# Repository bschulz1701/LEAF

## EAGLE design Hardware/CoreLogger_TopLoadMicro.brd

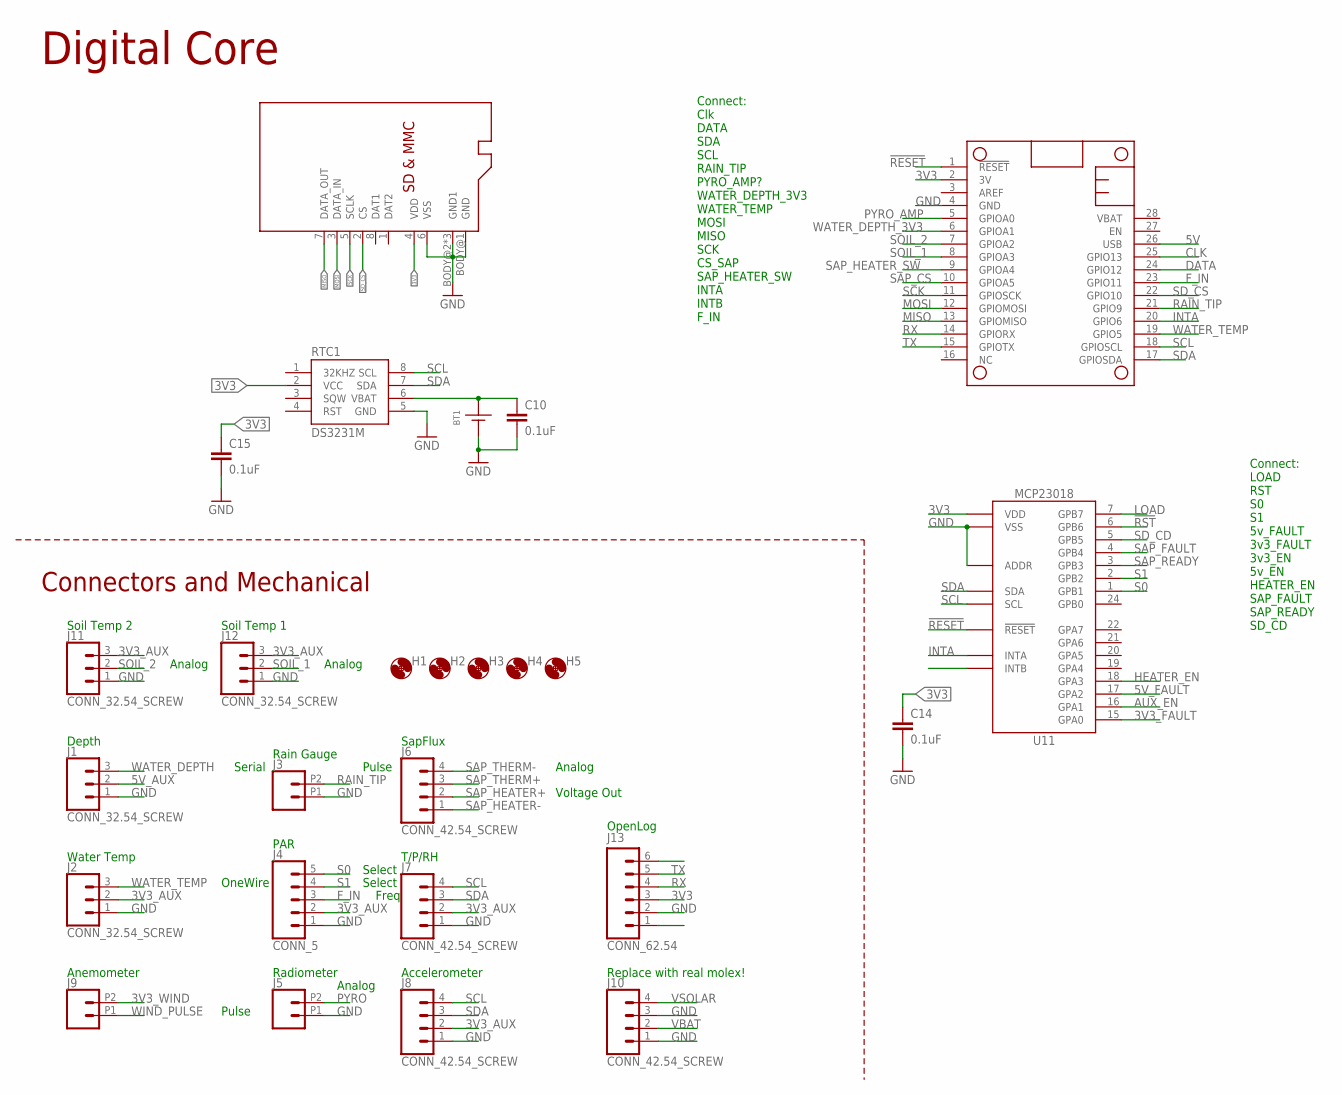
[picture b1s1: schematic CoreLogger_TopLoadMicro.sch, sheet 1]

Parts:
BT1: BATTERY_COIN12MM; LINX_BAT-HLD-012-SMT
C10: 0.1uF; C0603
C14, C15: 0.1uF; C0402
H1, H2, H3, H4, H5: MOUNTING_HOLE4_NP; 4_40
J1, J2, J11, J12: CONN_32.54_SCREW; 1X03_SCREW
J3, J5, J9: CONN_022.54_SCREW; 1X02_2.54_SCREWTERM
J4: CONN_5; 1X05
J6, J7, J8, J10: CONN_42.54_SCREW; 1X04_SCREW
J13: CONN_62.54; 1X06
MS1: FEATHERWING_NODIM; FEATHERWING_DIM
RTC1: DS3231M; SO08
SD1: MICROSD_NOCDHINDGED; USD_MOLEX_HINDGED
U11: MCP23018QFN; QFN24

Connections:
3V3: C14.1, C15.1, J13.3, MS1.2 (3V), RTC1.2 (VCC), SD1.4 (VDD), U11.8 (VDD); also elsewhere on the board
3V3_AUX: J2.2, J4.2, J7.2, J8.2, J11.3, J12.3; also elsewhere on the board
3V3_FAULT: U11.15 (GPA0); also elsewhere on the board
3V3_WIND: J9.P2 (2); also elsewhere on the board
5V: MS1.26 (USB); also elsewhere on the board
5V_AUX: J1.2; also elsewhere on the board
5V_FAULT: U11.17 (GPA2); also elsewhere on the board
!RESET: MS1.1 (!RESET), U11.12 (!RESET)
!RST: U11.6 (GPB6); also elsewhere on the board
AUX_EN: U11.16 (GPA1); also elsewhere on the board
CLK: MS1.25 (GPIO13); also elsewhere on the board
DATA: MS1.24 (GPIO12); also elsewhere on the board
F_IN: J4.3, MS1.23 (GPIO11)
GND: BT1.GND (-), C10.2, C14.2, C15.2, J1.1, J2.1, J3.P1 (1), J4.1, J5.P1 (1), J7.1, J8.1, J10.1, J10.3, J11.1, J12.1, J13.2, MS1.4 (GND), RTC1.5 (GND), SD1.6 (VSS), SD1.BODY@1 (GND), SD1.BODY@2 (GND1), SD1.BODY@3 (GND1), SD1.BODY@4 (GND1), U11.11 (ADDR), U11.23 (VSS); also elsewhere on the board
HEATER_EN: U11.18 (GPA3); also elsewhere on the board
INTA: MS1.20 (GPIO6), U11.14 (INTA)
LOAD: U11.7 (GPB7); also elsewhere on the board
MISO: MS1.13 (GPIOMISO), SD1.7 (DATA_OUT); also elsewhere on the board
MOSI: MS1.12 (GPIOMOSI), SD1.3 (DATA_IN); also elsewhere on the board
unnamed: BT1.POWER0 (+), BT1.POWER1 (+), C10.1, RTC1.6 (VBAT)
PYRO: J5.P2 (2); also elsewhere on the board
PYRO_AMP: MS1.5 (GPIOA0); also elsewhere on the board
RAIN_TIP: J3.P2 (2), MS1.21 (GPIO9); also elsewhere on the board
RX: J13.4, MS1.14 (GPIORX)
S0: J4.5, U11.1 (GPB1)
S1: J4.4, U11.2 (GPB2)
SAP_CS: MS1.10 (GPIOA5); also elsewhere on the board
SAP_FAULT: U11.4 (GPB4); also elsewhere on the board
SAP_HEATER+: J6.2; also elsewhere on the board
SAP_HEATER-: J6.1; also elsewhere on the board
SAP_HEATER_SW: MS1.9 (GPIOA4); also elsewhere on the board
SAP_READY: U11.3 (GPB3); also elsewhere on the board
SAP_THERM+: J6.3; also elsewhere on the board
SAP_THERM-: J6.4; also elsewhere on the board
SCK: MS1.11 (GPIOSCK), SD1.5 (SCLK); also elsewhere on the board
SCL: J7.4, J8.4, MS1.18 (GPIOSCL), RTC1.8 (SCL), U11.9 (SCL); also elsewhere on the board
SDA: J7.3, J8.3, MS1.17 (GPIOSDA), RTC1.7 (SDA), U11.10 (SDA); also elsewhere on the board
SD_CD: U11.5 (GPB5)
SD_CS: MS1.22 (GPIO10), SD1.2 (CS)
SOIL_1: J12.2, MS1.8 (GPIOA3)
SOIL_2: J11.2, MS1.7 (GPIOA2)
TX: J13.5, MS1.15 (GPIOTX)
VBAT: J10.2; also elsewhere on the board
VSOLAR: J10.4; also elsewhere on the board
WATER_DEPTH: J1.3; also elsewhere on the board
WATER_DEPTH_3V3: MS1.6 (GPIOA1); also elsewhere on the board
WATER_TEMP: J2.3, MS1.19 (GPIO5); also elsewhere on the board
WIND_PULSE: J9.P1 (1); also elsewhere on the board

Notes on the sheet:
Depth
Water Temp
Radiometer
PAR
Rain Gauge
Accelerometer
T/P/RH
SapFlux
OneWire
Serial
Pulse
Freq
Select
Analog
Voltage Out
Anemometer
Replace with real molex!
Connect: Clk DATA SDA SCL RAIN_TIP PYRO_AMP? WATER_DEPTH_3V3 WATER_TEMP MOSI MISO SCK CS_SAP SAP_HEATER_SW INTA INTB F_IN
Connect: LOAD RST S0 S1 5v_FAULT 3v3_FAULT 3v3_EN 5v_EN HEATER_EN SAP_FAULT SAP_READY SD_CD
Digital Core
Connectors and Mechanical
Soil Temp 2
Soil Temp 1
OpenLog

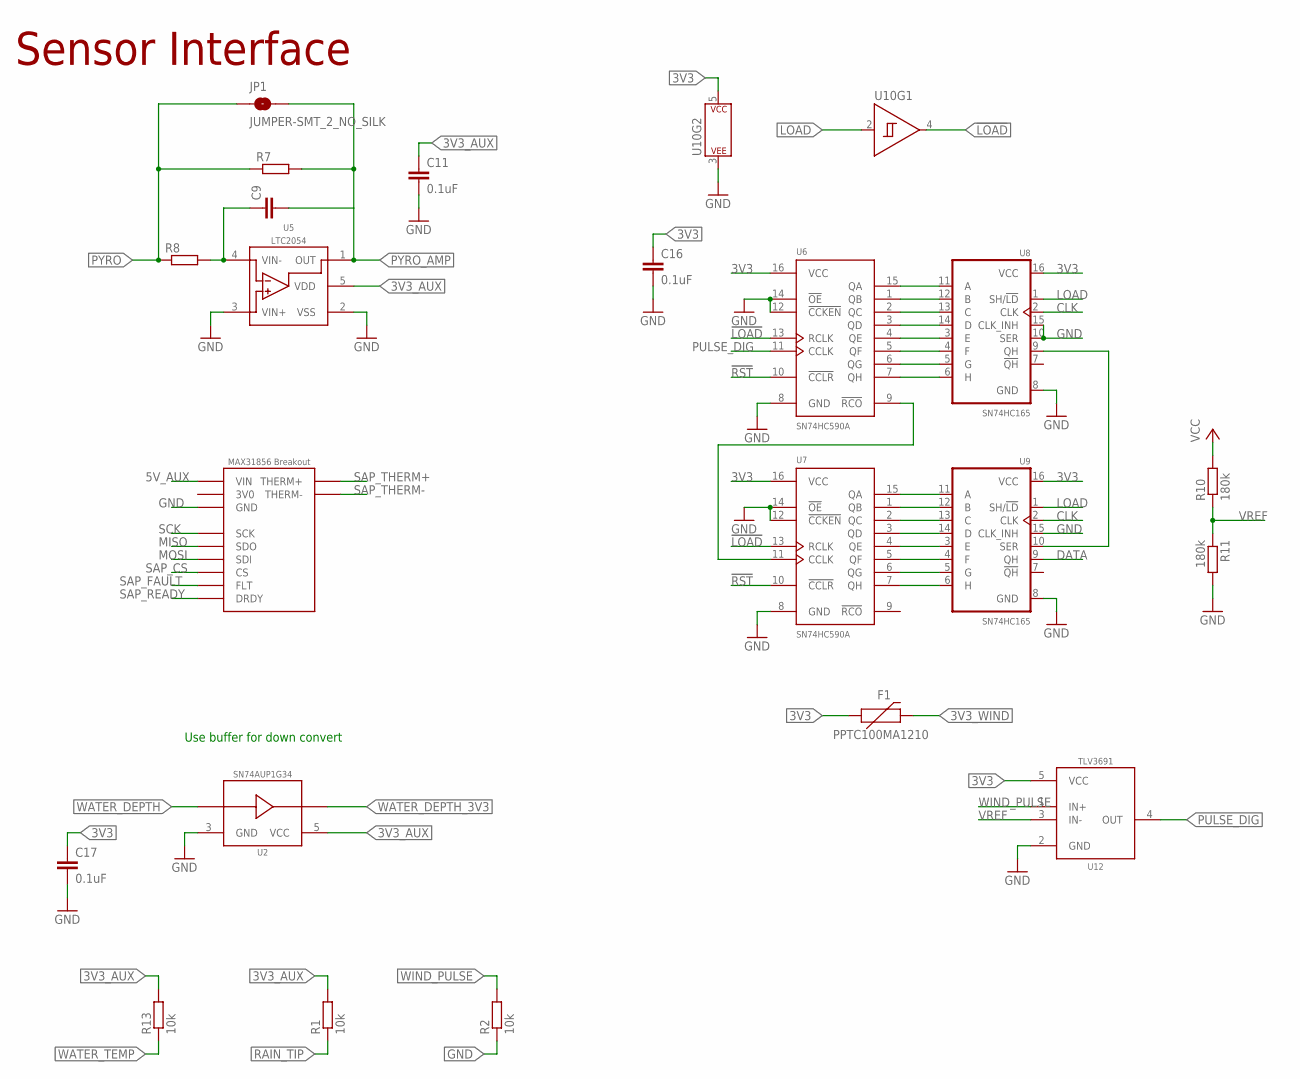
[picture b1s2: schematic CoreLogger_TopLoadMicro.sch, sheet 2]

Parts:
C9: C-EU1NFC0603; C0603
C11, C16, C17: 0.1uF; C0402
F1: PPTC100MA1210; 1210_BOURNS
JP1: JUMPER-SMT_2_NO_SILK; SMT-JUMPER_2_NO_SILK
R1, R2, R13: 10k; R0603
R7: R-EU_P27KR0603; R0603
R8: R-EU_1KR0603; R0603
R10, R11: 180k; R0603
U2: SN74AUP1G34SC70; DCK_R-PDSO-G5
U5: LTC2054; SOT23-5
U6, U7: SN74HC590AD; SO16
U8, U9: SN74HC165D; SO16
U10: SN74AUP1G14DCK; DCK_R-PDSO-G5
U12: TLV3691DCK; DCK_R-PDSO-G5
XU1: MAX31856_BREAKOUT

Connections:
3V0: XU1.3VO (3V0)
3V3: C16.1, C17.1, F1.1, R10.2, U6.16 (VCC), U7.16 (VCC), U8.16 (VCC), U9.16 (VCC), U10.5 (P$V+), U12.5 (VCC); also elsewhere on the board
3V3_AUX: C11.1, R1.2, R13.2, U2.5 (VCC), U5.5 (VDD); also elsewhere on the board
3V3_WIND: F1.2; also elsewhere on the board
5V_AUX: XU1.VIN; also elsewhere on the board
!LOAD: U6.13 (RCLK), U7.13 (RCLK), U10.4 (Y)
!RST: U6.10 (!CCLR), U7.10 (!CCLR); also elsewhere on the board
CLK: U8.2 (CLK), U9.2 (CLK); also elsewhere on the board
DATA: U9.9 (QH); also elsewhere on the board
GND: C11.2, C16.2, C17.2, R2.1, R11.2, U2.3 (GND), U5.2 (VSS), U5.3 (VIN+), U6.8 (GND), U6.12 (!CCKEN), U6.14 (!OE), U7.8 (GND), U7.12 (!CCKEN), U7.14 (!OE), U8.8 (GND), U8.10 (SER), U8.15 (CLK_INH), U9.8 (GND), U9.15 (CLK_INH), U10.3 (P$V-), U12.2 (GND), XU1.GND; also elsewhere on the board
LOAD: U8.1 (SH/!LD), U9.1 (SH/!LD), U10.2 (A); also elsewhere on the board
MISO: XU1.SDO; also elsewhere on the board
MOSI: XU1.SDI; also elsewhere on the board
unnamed: C9.1, R8.2, U5.4 (VIN-)
unnamed: U7.15 (QA), U9.11 (A)
unnamed: U7.1 (QB), U9.12 (B)
unnamed: U7.2 (QC), U9.13 (C)
unnamed: U7.3 (QD), U9.14 (D)
unnamed: U7.4 (QE), U9.3 (E)
unnamed: U7.5 (QF), U9.4 (F)
unnamed: U7.6 (QG), U9.5 (G)
unnamed: U7.7 (QH), U9.6 (H)
unnamed: U6.7 (QH), U8.6 (H)
unnamed: U6.6 (QG), U8.5 (G)
unnamed: U6.5 (QF), U8.4 (F)
unnamed: U6.4 (QE), U8.3 (E)
unnamed: U6.3 (QD), U8.14 (D)
unnamed: U6.2 (QC), U8.13 (C)
unnamed: U6.1 (QB), U8.12 (B)
unnamed: U6.15 (QA), U8.11 (A)
unnamed: U8.9 (QH), U9.10 (SER)
unnamed: U6.9 (!RCO), U7.11 (CCLK)
PULSE_DIG: U6.11 (CCLK), U12.4 (OUT)
PYRO: JP1.1, R7.1, R8.1; also elsewhere on the board
PYRO_AMP: C9.2, JP1.2, R7.2, U5.1 (OUT); also elsewhere on the board
RAIN_TIP: R1.1; also elsewhere on the board
SAP_CS: XU1.CS; also elsewhere on the board
SAP_FAULT: XU1.FLT; also elsewhere on the board
SAP_READY: XU1.DRDY; also elsewhere on the board
SAP_THERM+: XU1.THERM+; also elsewhere on the board
SAP_THERM-: XU1.THERM-; also elsewhere on the board
SCK: XU1.SCK; also elsewhere on the board
VREF: R10.1, R11.1, U12.3 (IN-)
WATER_DEPTH: U2.2 (A); also elsewhere on the board
WATER_DEPTH_3V3: U2.4 (Y); also elsewhere on the board
WATER_TEMP: R13.1; also elsewhere on the board
WIND_PULSE: R2.2, U12.1 (IN+); also elsewhere on the board

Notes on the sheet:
Use buffer for down convert
Sensor Interface

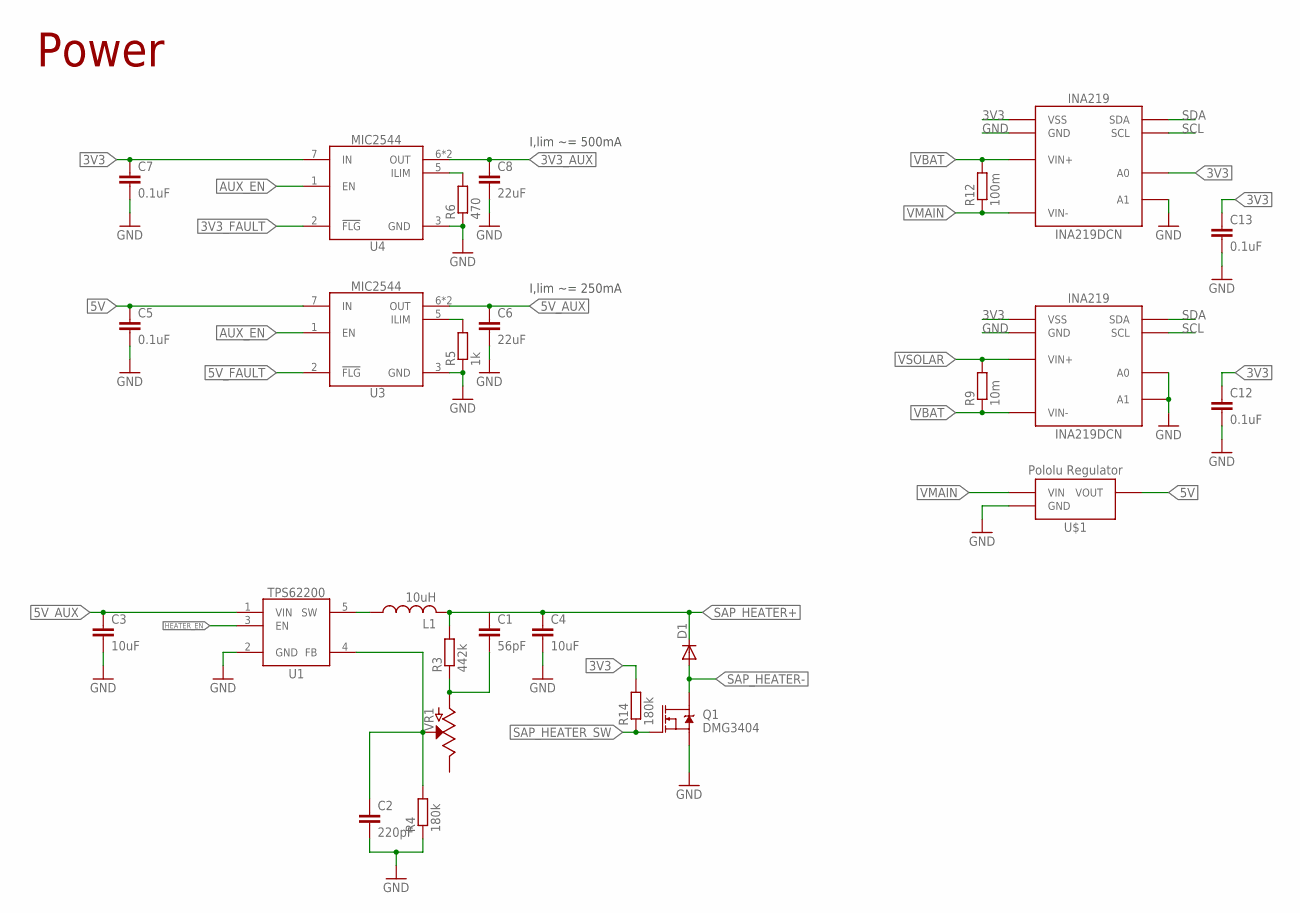
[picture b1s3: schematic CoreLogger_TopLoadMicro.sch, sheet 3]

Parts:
C1: 56pF; C0402
C2: 220pF; C0402
C3, C4: 10uF; C0805
C5, C7, C12, C13: 0.1uF; C0402
C6, C8: 22uF; C0805
D1: DIODESOD-123; SOD-123; MPN 1N4448W-TP; DIGIKEY 1N4448WTPMSCT-ND
L1: 10uH; WE-LQS(4X4); MPN 74404043100A; DIGIKEY 732-10757-1-ND
Q1: DMG3404; SOT23-3
R3: 442k; R0603
R4, R14: 180k; R0603
R5: 1k; R0603
R6: 470; R0603
R9: 10m; R0805
R12: 100m; R0805
U1: TPS62200SOT23; DBV0005A
U3, U4: MIC2544MSOP; MSOP_8
U13, U14: INA219DCN; DCN_R-PDSO-G8
U$1: POLOLU_REGULATOR; U1V10FX_REGULATOR
VR1: POTENTIOMETER3214W; POT_3214W; MPN 3214W-1-204E; DIGIKEY 3214W-1-204ECT-ND

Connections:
3V3: C7.1, C12.1, C13.1, R14.2, U4.7 (IN), U13.4 (VSS), U14.4 (VSS), U14.7 (A0); also elsewhere on the board
3V3_AUX: C8.1, U4.6 (OUT), U4.8 (OUT); also elsewhere on the board
3V3_FAULT: U4.2 (!FLG); also elsewhere on the board
5V: C5.1, U3.7 (IN), U$1.VOUT; also elsewhere on the board
5V_AUX: C3.1, C6.1, U1.1 (VIN), U3.6 (OUT), U3.8 (OUT); also elsewhere on the board
5V_FAULT: U3.2 (!FLG); also elsewhere on the board
AUX_EN: U3.1 (EN), U4.1 (EN); also elsewhere on the board
GND: C2.2, C3.2, C4.2, C5.2, C6.2, C7.2, C8.2, C12.2, C13.2, Q1.2 (S), R4.1, R5.1, R6.1, U1.2 (GND), U3.3 (GND), U4.3 (GND), U13.3 (GND), U13.7 (A0), U13.8 (A1), U14.3 (GND), U14.8 (A1), U$1.GND; also elsewhere on the board
HEATER_EN: U1.3 (EN); also elsewhere on the board
unnamed: C1.2, R3.1, VR1.1 (A)
unnamed: C2.1, R4.2, U1.4 (FB), VR1.2 (S)
unnamed: R6.2, U4.5 (ILIM)
unnamed: R5.2, U3.5 (ILIM)
unnamed: L1.P$1 (1), U1.5 (SW)
SAP_HEATER+: C1.1, C4.1, D1.CAT (C), L1.P$2 (2), R3.2; also elsewhere on the board
SAP_HEATER-: D1.ANODE (A), Q1.3 (D); also elsewhere on the board
SAP_HEATER_SW: Q1.1 (G), R14.1; also elsewhere on the board
SCL: U13.5 (SCL), U14.5 (SCL); also elsewhere on the board
SDA: U13.6 (SDA), U14.6 (SDA); also elsewhere on the board
VBAT: R9.1, R12.2, U13.2 (VIN-), U14.1 (VIN+); also elsewhere on the board
VMAIN: R12.1, U14.2 (VIN-), U$1.VIN
VSOLAR: R9.2, U13.1 (VIN+); also elsewhere on the board

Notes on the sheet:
Power
I,lim ~= 500mA
I,lim ~= 250mA

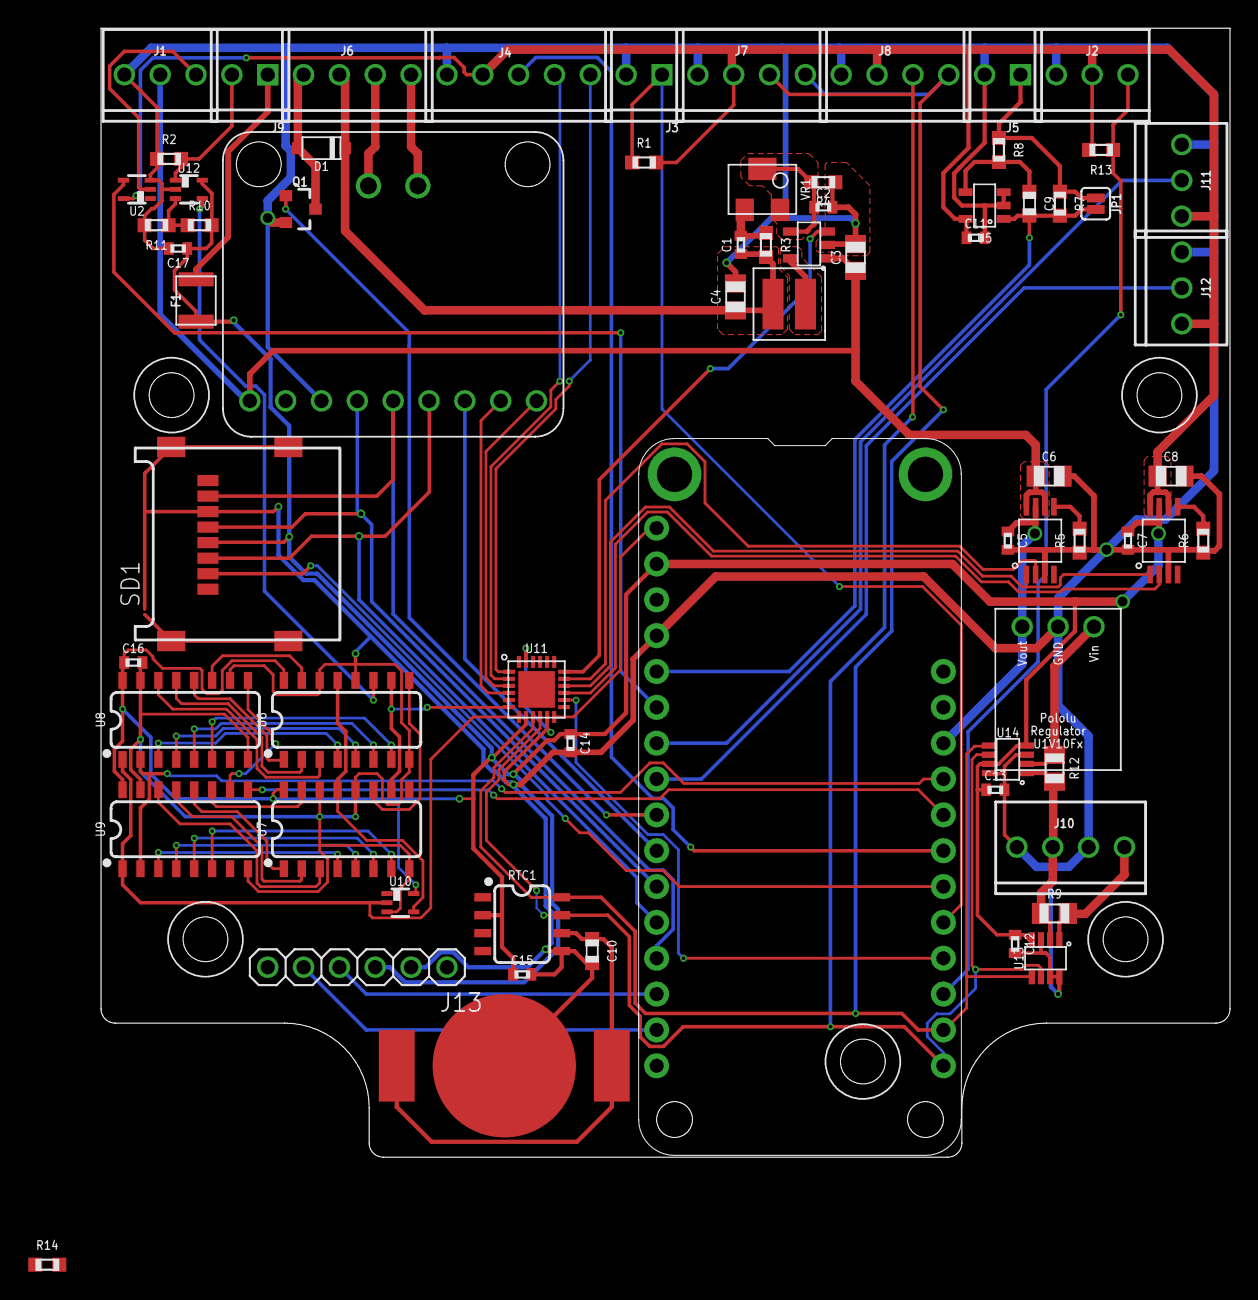
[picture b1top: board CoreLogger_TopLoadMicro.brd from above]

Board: 2 copper layers, 80.0 x 80.0 mm, 75 parts (0 on the bottom side), 75 nets.

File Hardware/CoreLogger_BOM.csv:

Qty,Value,Device,Package,Parts,Description,DIGIKEY,DISP,MF,MPN,VALUE,VALUE_PART
1,,C-EU1NFC0603,C0603,C9,"CAPACITOR, European symbol",311-1080-1-ND,,Yageo,CC0603KRX7R9BB102,,
3,,CONN_022.54_SCREW,1X02_2.54_SCREWTERM,"J3, J5, J9",Genaric 2 terminal header,ED10561-ND,,OnShore,OSTVN02A150,,
1,,DIODESOD-123,SOD-123,D1,Genaric Diode,1N4448WTPMSCT-ND,,Micro Commercial,1N4448W-TP,,
5,,MOUNTING_HOLE4_NP,4_40,"H1, H2, H3, H4, H5",Genaric Mechanical Mounting Hole,,,,,,
2,,R-EU_1KR0603,R0603,"R5, R8","RESISTOR, European symbol",311-1KLDCT-ND,,Yageo,AC0603FR-071KL,,1k
1,,R-EU_470R0603,R0603,R6,"RESISTOR, European symbol",311-470HRCT-ND,,Yageo,RC0603FR-07470RL,,470
1,,R-EU_P27KR0603,R0603,R7,"RESISTOR, European symbol",P27KDBCT-ND,,Panasonic,ERA-3AEB273V,,27k
1,,SN74AUP1G14DCK,DCK_R-PDSO-G5,U10,SN74x1G14 - Single Schmitt Triger Inverter,296-19076-1-ND,,TI,SN74AUP1G14DCKR,,
2,,SN74HC165D,SO16,"U8, U9",SN74HC165 - 8 bit PISO shift register,296-8250-1-ND,,TI,SN74HC165DR,,
2,,SN74HC590AD,SO16,"U6, U7",SN74HC590A - 8 bit binary counter with direct clear,296-8340-5-ND,,TI,SN74HC590AD,,
9,0.1uF,C-EU0.1UFC0402,C0402,"C5, C7, C11, C12, C13, C14, C15, C16, C17","CAPACITOR, European symbol",490-4759-1-ND,,Murata,GCM155R71C104KA55D,,
1,0.1uF,C-EU0.1UFC0603,C0603,C10,"CAPACITOR, European symbol",490-6051-1-ND,,Murata,GCM188R71E104KA57D,,
1,100m,R-EU_0.1R0805,R0805,R12,"RESISTOR, European symbol",P19308CT-ND,,Panasonic,ERJ-6DSFR10V,,
3,10k,R-EU_10KR0603,R0603,"R1, R2, R13","RESISTOR, European symbol",311-10.0KHRCT-ND,,Yageo,RC0603FR-0710KL,,10k
1,10m,R-EU_0.01R0805,R0805,R9,"RESISTOR, European symbol",CRF0805-FZ-R010ELFCT-ND,,Bourns,CRF0805-FZ-R010ELF,,
2,10uF,C-EU10UFC0805,C0805,"C3, C4","CAPACITOR, European symbol",490-6473-6-ND,,Murata,GRM21BR61C106KE15K,,
1,10uH,INDUCTORLQS_4X4,WE-LQS(4X4),L1,Genaric inductor,732-10757-1-ND,,Wurth,74404043100A,,
3,180k,R-EU_180KR0603,R0603,"R4, R10, R11","RESISTOR, European symbol",P180KHCT-ND,,Panasonic,ERJ-3EKF1803V,,180k
1,220pF,C-EU220PFC0402,C0402,C2,"CAPACITOR, European symbol",587-1215-1-ND,,Taiyo Yuden,UMK105CG221JV-F,,
2,22uF,C-EU22UFC0805,C0805,"C6, C8","CAPACITOR, European symbol",490-9952-1-ND,,Murata,GRM219R61C226ME15L,,
1,442k,R-EU_422KR0603,R0603,R3,"RESISTOR, European symbol",311-422KHRCT-ND,,Yageo,RC0603FR-07422KL,,422k
1,56pF,C-EU56PFC0402,C0402,C1,"CAPACITOR, European symbol",311-1022-1-ND,,Yageo,CC0402JRNPO9BN560,,
1,BATTERY_COIN12MM,BATTERY_COIN12MM,LINX_BAT-HLD-012-SMT,BT1,Coin Cell Battery Holder,BAT-HLD-012-SMT-ND,,Linx,BAT-HLD-012-SMT,,
4,CONN_32.54_SCREW,CONN_32.54_SCREW,1X03_SCREW,"J1, J2, J11, J12",Genaric 3 terminal header,ED10562-ND,,On Shore,OSTVN03A150,,
4,CONN_42.54_SCREW,CONN_42.54_SCREW,1X04_SCREW,"J6, J7, J8, J10",Genaric 4 terminal header,ED10563-ND,,On Shore,OSTVN04A150,,
1,CONN_5,CONN_5,1X05,J4,Genaric 5 terminal header,ED10564-ND,,On Shore,OSTVN05A150,,
1,CONN_62.54,CONN_62.54,1X06,J13,Genaric 6 terminal header,,,,,,
1,DMG3404,MOSFET-NCH-DMG3404L,SOT23-3,Q1,N-channel MOSFETs,DMG3404L-7DICT-ND,,Diodes Incorporated,DMG3404L-7,DMG3404,
1,DS3231M,DS3231M,SO08,RTC1,DS3231M Real Time Clock,DS3231MZ+-ND,,Maxim,DS3231MZ+,,
1,FEATHERWING_NODIM,FEATHERWING_NODIM,FEATHERWING_DIM,MS1,,,,,,,
2,INA219DCN,INA219DCN,DCN_R-PDSO-G8,"U13, U14",INA219 - Zero Drift Bidirectional Current/Power Monitor with I2C Interface,296-23770-1-ND,,TI,INA219AIDCNR,,
1,JUMPER-SMT_2_NO_SILK,JUMPER-SMT_2_NO_SILK,SMT-JUMPER_2_NO_SILK,JP1,Normally open jumper,,,,,,
1,LTC2054,LTC2054,SOT23-5,U5,LTC2054 -Single Micropower Zero Drift Op-Amp,LTC2054HS5#TRMPBFCT-ND,LTC2054,LT,LTC2054HS5#TRMPBF,,
1,MAX31856_BREAKOUT,MAX31856_BREAKOUT,MAX31856_BREAKOUT,XU1,Socket for MAX31856 Breakout from Adafruit,,,,,,
1,MCP23018QFN,MCP23018QFN,QFN24,U11,"MCP23018 - I2C I/O Expander, 16 bit wtih interrupt and reset",MCP23018T-E/MJCT-ND,,TI,MCP23018T-E/MJ,,
2,MIC2544MSOP,MIC2544MSOP,MSOP_8,"U3, U4","MIC2544/48 - Hight Side Load Switch, with Adjustable Current Limit",576-1738-5-ND,,Microchip,MIC2544-1YMM,,
1,MICROSD_NOCDHINDGED,MICROSD_NOCDHINDGED,USD_MOLEX_HINDGED,SD1,"Micro-SD / Transflash card holder with SPI pinout, No Card Detect",WM6698CT-ND,,Molex,472192001,,
1,POLOLU_REGULATOR,POLOLU_REGULATOR,U1V10FX_REGULATOR,U$1,,,,,,,
1,POTENTIOMETER3214W,POTENTIOMETER3214W,POT_3214W,VR1,Genaric potentiometer,3214W-1-204ECT-ND,,Bourns,3214W-1-204E,,
1,PPTC100MA1210,PPTC100MA1210,1210_BOURNS,F1,Resettable Fuse PPTC,MF-USMF005-2CT-ND,,Bourns,MF-USMF005-2,,
1,SN74AUP1G34SC70,SN74AUP1G34SC70,DCK_R-PDSO-G5,U2,SN74AUP1G34 - Logic Buffer,296-17230-1-ND,,TI,SN74LVC1G34DCKR,,
1,TLV3691DCK,TLV3691DCK,DCK_R-PDSO-G5,U12,TLV3691 - Nanopower Analog Comparator,296-37910-1-ND,,TI,TLV3691IDCKR,,
1,TPS62200SOT23,TPS62200SOT23,DBV0005A,U1,TPS6220x - High Efficiency Synchronous Step-Down Converter (Buck),296-12716-1-ND,TPS62200,TI,TPS62200DBVR,,
1,2.2nF,,,,,311-1081-1-ND,,Yageo,CC0603KRX7R9BB222,,
1,380pF,,,,,311-1188-1-ND,,Yageo,CC0603KRX7R9BB681,,

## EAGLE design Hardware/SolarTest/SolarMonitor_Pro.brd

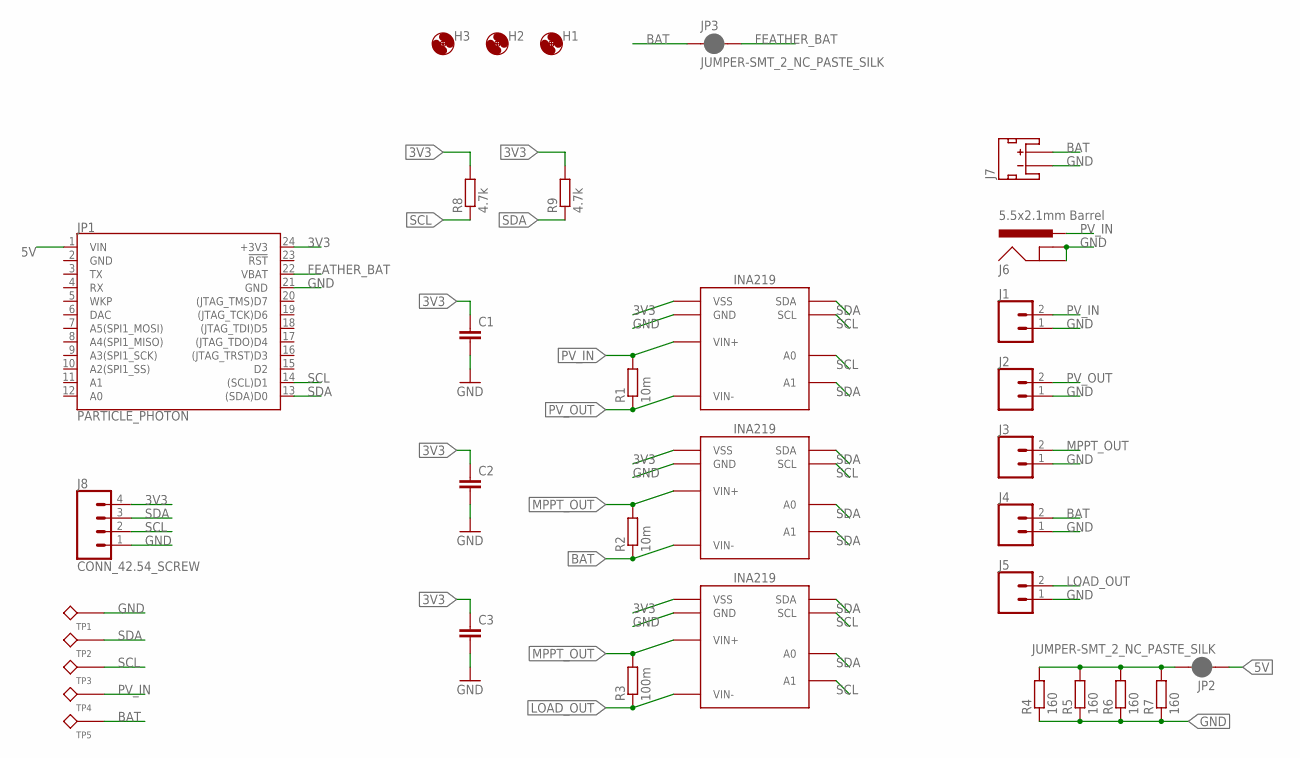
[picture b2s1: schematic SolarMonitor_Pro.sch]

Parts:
C1, C2, C3: C-EU0.1UFC0402; C0402
H1, H2, H3: MOUNTING_HOLE4_NP; 4_40
J1, J2, J3, J4, J5: CONN_023.5MM; SCREWTERMINAL-3.5MM-2
J6: 5.5x2.1mm Barrel; POWER_JACK_SMD
J7: JST_2MM_MALE; JST-2-SMD
J8: CONN_42.54_SCREW; 1X04_SCREW
JP1: PARTICLE_PHOTON
JP2, JP3: JUMPER-SMT_2_NC_PASTE_SILK; SMT-JUMPER_2_NC_PASTE_SILK
R1, R2: 10m; R0805
R3: 100m; R0805
R4, R5, R6, R7: 160; R1206
R8, R9: 4.7k; R0402
TP1, TP2, TP3, TP4, TP5: TESTPOINTRCU; TESTPOINT_0603
U1, U2, U3: INA219DCN; DCN_R-PDSO-G8

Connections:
3V3: C1.1, C2.1, C3.1, J8.4, JP1.24 (+3V3), R8.2, R9.2, U1.4 (VSS), U2.4 (VSS), U3.4 (VSS)
5V: JP1.1 (VIN), JP2.1
BAT: J4.2, J7.2 (+), JP3.1, R2.1, TP5.1, U2.2 (VIN-)
FEATHER_BAT: JP1.22 (VBAT), JP3.2
GND: C1.2, C2.2, C3.2, J1.1, J2.1, J3.1, J4.1, J5.1, J6.GND (GNDBREAK), J6.P$4 (GND), J7.1 (-), J8.1, JP1.2 (GND), JP1.21 (GND), R4.1, R5.1, R6.1, R7.1, TP1.1, U1.3 (GND), U2.3 (GND), U3.3 (GND)
LOAD: JP2.2, R4.2, R5.2, R6.2, R7.2
LOAD_OUT: J5.2, R3.1, U3.2 (VIN-)
MPPT_OUT: J3.2, R2.2, R3.2, U2.1 (VIN+), U3.1 (VIN+)
PV_IN: J1.2, J6.VIN0 (PWR), R1.2, TP4.1, U1.1 (VIN+)
PV_OUT: J2.2, R1.1, U1.2 (VIN-)
SCL: J8.2, JP1.14 ((SCL)D1), R8.1, TP3.1, U1.5 (SCL), U1.7 (A0), U2.5 (SCL), U3.5 (SCL), U3.8 (A1)
SDA: J8.3, JP1.13 ((SDA)D0), R9.1, TP2.1, U1.6 (SDA), U1.8 (A1), U2.6 (SDA), U2.7 (A0), U2.8 (A1), U3.6 (SDA), U3.7 (A0)

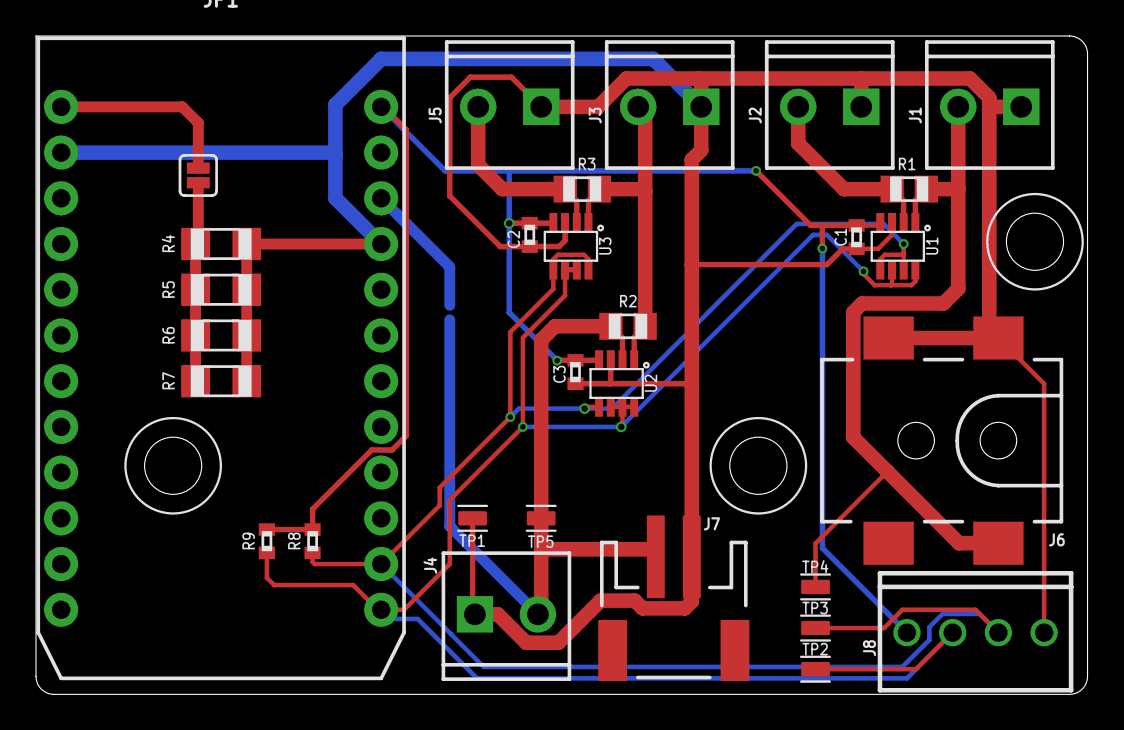
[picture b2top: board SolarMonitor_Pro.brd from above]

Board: 2 copper layers, 58.4 x 36.6 mm, 34 parts (1 on the bottom side), 12 nets.

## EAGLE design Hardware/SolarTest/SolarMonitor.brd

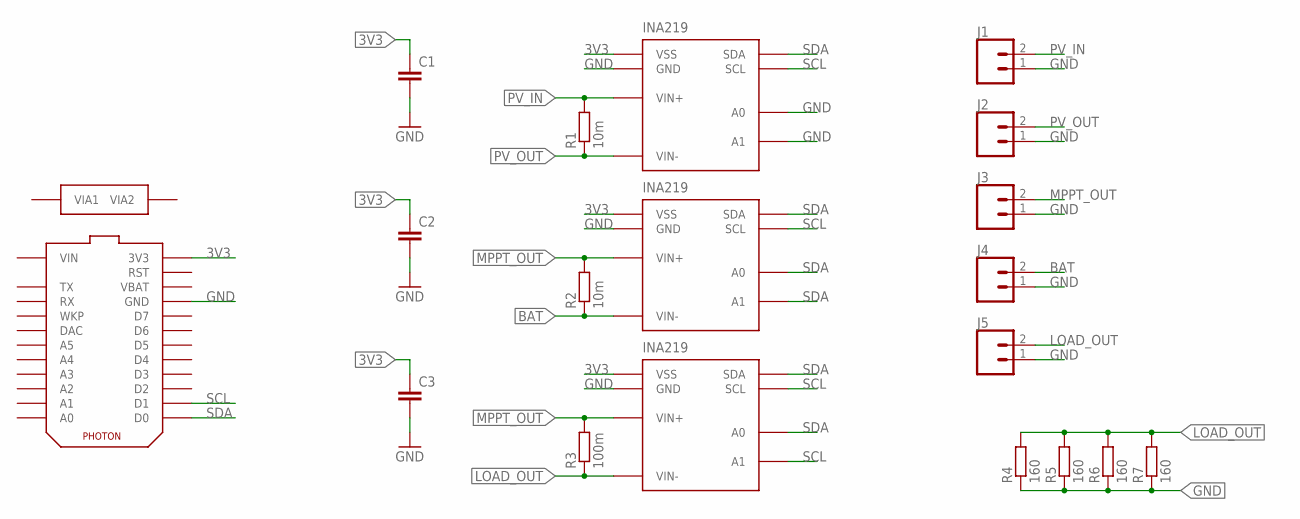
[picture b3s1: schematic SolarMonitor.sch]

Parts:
C1, C2, C3: C-EU0.1UFC0603; C0603
J1, J2, J3, J4, J5: CONN_023.5MM; SCREWTERMINAL-3.5MM-2
R1, R2: 10m; R0805
R3: 100m; R0805
R4, R5, R6, R7: 160; R1206
U$1: TEMPLATE_PHOTON_RAW; PHOTON_RAW
U$2, U$3, U$4: INA219; SOIC_8

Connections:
3V3: C1.1, C2.1, C3.1, U$1.3V3, U$1.3V3. (3V3), U$1.3V31 (3V3), U$2.5 (VSS), U$3.5 (VSS), U$4.5 (VSS)
BAT: J4.2, R2.1, U$3.7 (VIN-)
GND: C1.2, C2.2, C3.2, J1.1, J2.1, J3.1, J4.1, J5.1, R4.1, R5.1, R6.1, R7.1, U$1.GND, U$1.GND1 (GND), U$1.GND. (GND), U$1.GND.@1 (GND), U$1.GND@1 (GND), U$1.GND@2 (GND), U$2.1 (A1), U$2.2 (A0), U$2.6 (GND), U$3.6 (GND), U$4.6 (GND)
LOAD_OUT: J5.2, R3.1, R4.2, R5.2, R6.2, R7.2, U$4.7 (VIN-)
MPPT_OUT: J3.2, R2.2, R3.2, U$3.8 (VIN+), U$4.8 (VIN+)
PV_IN: J1.2, R1.2, U$2.8 (VIN+)
PV_OUT: J2.2, R1.1, U$2.7 (VIN-)
SCL: U$1.D1, U$1.D1. (D1), U$1.D1@1 (D1), U$2.4 (SCL), U$3.4 (SCL), U$4.1 (A1), U$4.4 (SCL)
SDA: U$1.D0, U$1.D0. (D0), U$1.D0@1 (D0), U$2.3 (SDA), U$3.1 (A1), U$3.2 (A0), U$3.3 (SDA), U$4.2 (A0), U$4.3 (SDA)

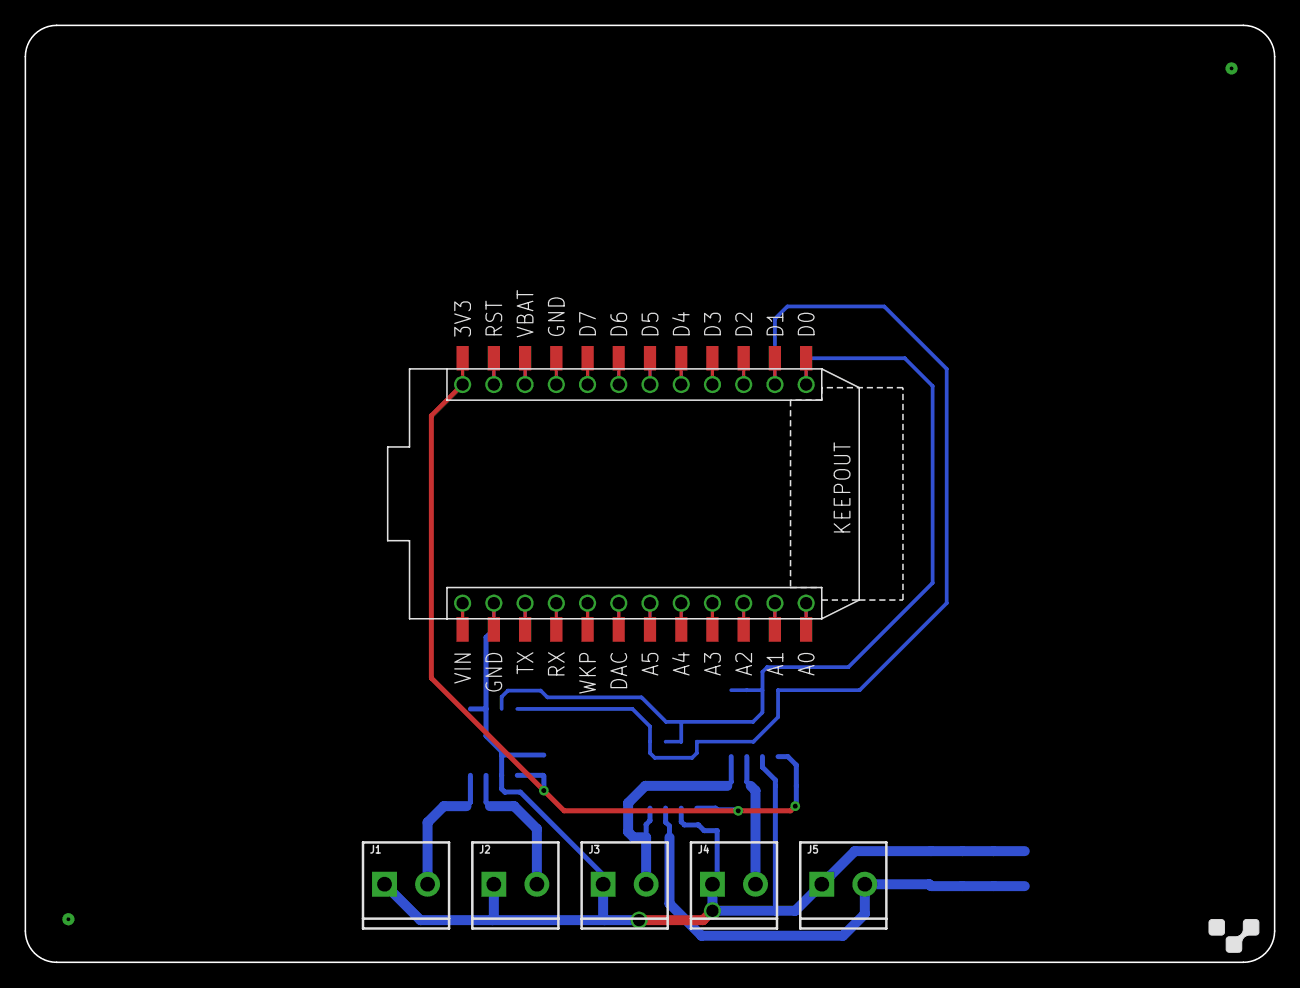
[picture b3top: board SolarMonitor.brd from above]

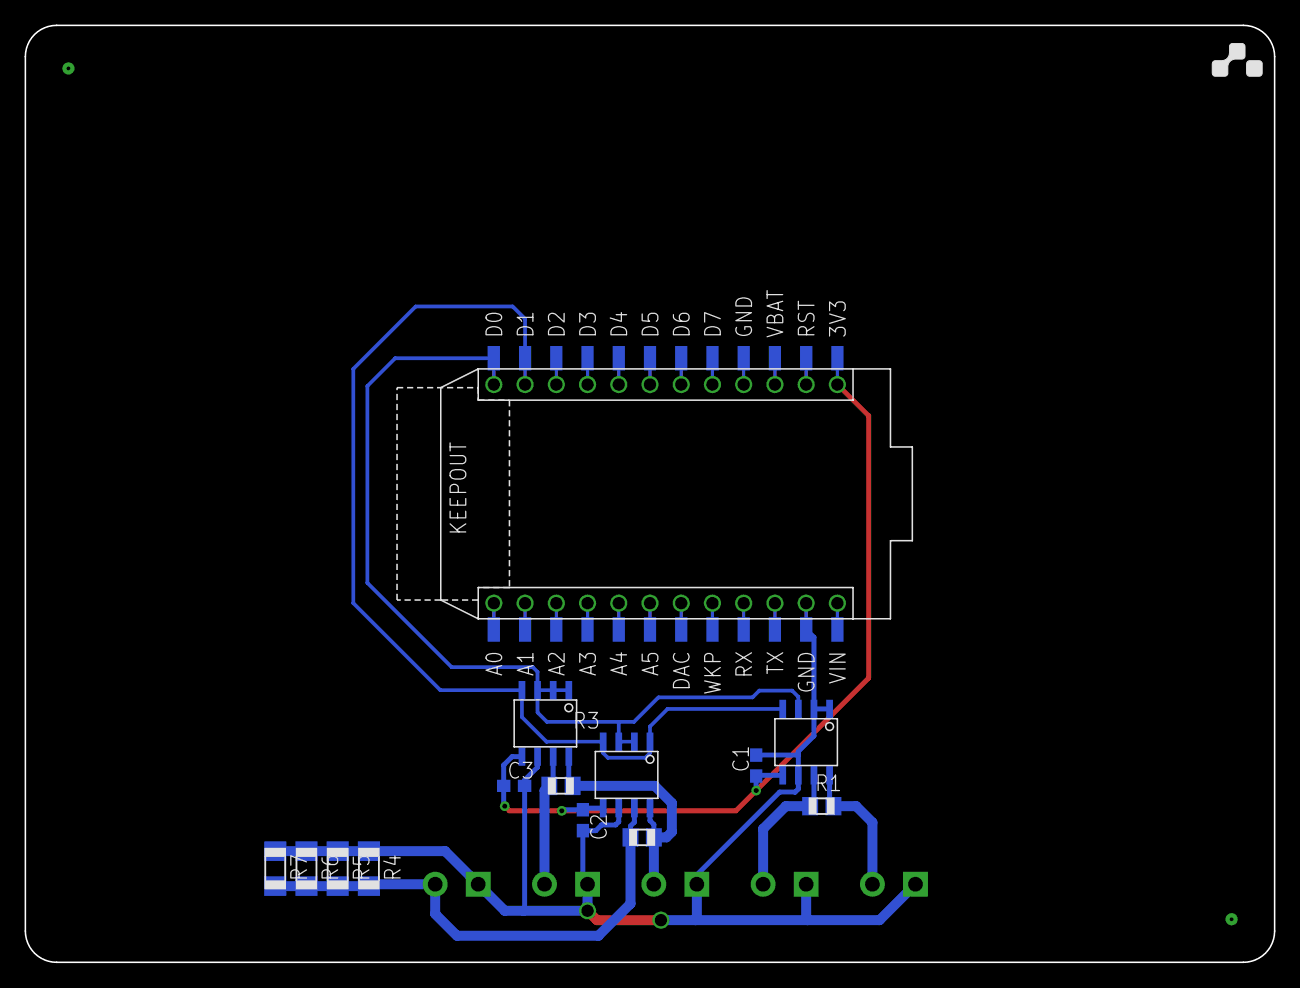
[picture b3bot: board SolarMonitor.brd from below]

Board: 2 copper layers, 101.6 x 76.2 mm, 19 parts (13 on the bottom side), 9 nets.

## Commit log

2019-03-18 Added initial design for Solar Measurement system
    Added v0 design for solar measurement prototype
2019-03-18 Added Voltera compatible gerbers
2019-03-19 Added Solar Monitor layout for external mfg
    Added Solar Monitor for OSH Park Manufacture, final layout required
2019-03-19 Updated solar monitor board, v0 ready for fab
2019-03-21 Final cleanup/part number for solar monitor v0
2019-04-02 Added git LFS
2019-04-02 Added additional PDF LFS attributes
2019-04-02 Fixed gif lfs typo
2019-04-02 Removed function of git lfs
    Evidently git lfs is not available on public forks, so unable to be used in this module
2019-04-19 Added ALPHA design for core logger
    Added very preliminary schematic design for core data logger, significant additions needed
2019-04-20 Added preliminary block diagrams
2019-04-21 Added Eagle library, continued logger designs
2019-04-21 Routing and minor design updates
    The majority of functionality is present, passes DRC, need to add polygons and test points, along with labeling
2019-04-22 Further updates, ready for final review
    Added silkscreen and minor layout improvements
2019-04-22 Generated optional board designs, generated gerbers
2019-04-23 Added BoM info and software for Lidar Lite interface
    Updated the BoM information in Eagle and generated csv, also added software for LidarLite interface system
2019-04-25 Updated LidarLite code
    Improved Lidar lite code to reduce power consumption and improve stability
2019-04-26 General schematic cleanup on logger board
2019-05-06 Minor cleanup
2019-05-06 Added Sap Heater FET pullup
    Added gate pullup to the FET drive on the sap heater power system
2019-07-09 Added BOM, added ADR info to schematic

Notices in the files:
parts and their libraries:
SparkFun-Jumpers: Licensing: Creative Commons ShareAlike 4.0 International - https://creativecommons.org/licenses/by-sa/4.0
bschulz: This work is licensed under the Creative Commons Attribution-ShareAlike 4.0
http://creativecommons.org/licenses/by-sa/4.0
